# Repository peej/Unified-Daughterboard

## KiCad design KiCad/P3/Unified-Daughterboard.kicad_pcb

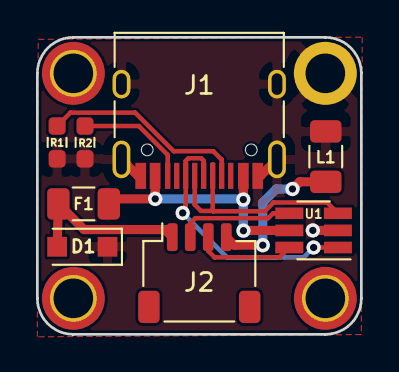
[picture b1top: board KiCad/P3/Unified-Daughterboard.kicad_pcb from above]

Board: 2 copper layers, 18.0 x 16.5 mm, 13 parts (1 on the bottom side), 10 nets.

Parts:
D1: SMF9.0CA; D_SOD-123F
F1: ASMD1206-150; Fuse_1206_3216Metric
G1: Unified-Daughterboard-Logo; Unified-Daughterboard-Logo.pretty
J1: USB_C_Receptacle_USB2.0; USB_C_Receptacle_HRO_TYPE-C-31-M-12
J2: SM04B-SRSS-TB(LF)(SN); JST_SH_SM04B-SRSS-TB_1x04-1MP_P1.00mm_Horizontal
L1: 60R@100MHz; L_1206_3216Metric
MH1, MH3, MH4: Mount-M2; MountingHole_2.2mm_M2_Pad_TopOnly
MH2: Mount-M2; MountingHole_2.2mm_M2_Pad
R1, R2: 5.1k; R_0603_1608Metric_Pad0.98x0.95mm_HandSolder
U1: USBLC6-2SC6; SOT-23-6_Handsoldering

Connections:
D+: J1.A6, J1.B6, U1.1
D-: J1.A7, J1.B7, U1.3
DN: J2.2, U1.4
DP: J2.3, U1.6
GND: J2.4, L1.1
GNDPWR: D1.1, J1.A1, J1.A12, J1.B1, J1.B12, J1.S1, L1.2, MH2.1, R1.2, R2.2, U1.2
unnamed: J1.A5, R1.1
unnamed: J1.B5, R2.1
VBUS: F1.1, J1.A4, J1.A9, J1.B4, J1.B9, U1.5
VCC: D1.2, F1.2, J2.1

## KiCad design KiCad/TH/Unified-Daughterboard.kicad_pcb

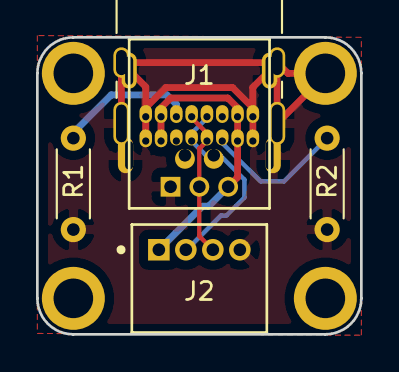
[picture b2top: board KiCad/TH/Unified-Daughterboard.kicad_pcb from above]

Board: 2 copper layers, 18.0 x 16.5 mm, 8 parts (0 on the bottom side), 6 nets.

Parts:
J1: HRO-TYPE-C-31-M-12; USB_Hybrid
J2: Conn_01x04; JST-S4B-ZRLFSN-0-0-MFG
MH1, MH2, MH3, MH4: Mount-M2; Generic-Mounthole
R1, R2: 5.1k; R_Axial_DIN0204_L3.6mm_D1.6mm_P5.08mm_Horizontal

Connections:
D+: J1.A6, J1.B6, J2.3
D-: J1.A7, J1.B7, J2.2
GND: J1.A1, J1.A12, J1.B1, J1.B12, J1.S1, J2.4, MH2.1, R1.2, R2.2
unnamed: J1.A5, R2.1
unnamed: J1.B5, R1.1
VCC: J1.A4, J1.A9, J1.B4, J1.B9, J2.1

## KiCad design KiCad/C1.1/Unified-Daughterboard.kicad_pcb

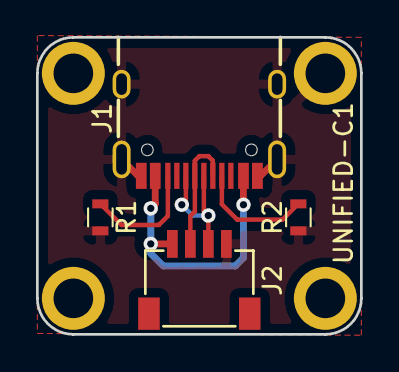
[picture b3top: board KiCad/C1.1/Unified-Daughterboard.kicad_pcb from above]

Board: 2 copper layers, 18.0 x 16.5 mm, 8 parts (0 on the bottom side), 6 nets.

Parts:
J1: HRO-TYPE-C-31-M-12; HRO-TYPE-C-31-M-12-Assembly
J2: Conn_01x04; JST-SR-4
MH1, MH2, MH3, MH4: Mount-M2; Generic-Mounthole
R1, R2: 5.1k; R_0603

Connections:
D+: J1.6, J1.8, J2.3
D-: J1.5, J1.7, J2.2
GND: J1.1, J1.12, J1.13, J2.4, MH2.1, R1.2, R2.2
unnamed: J1.4, R2.1
unnamed: J1.10, R1.1
VCC: J1.2, J1.11, J2.1

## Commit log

2021-09-17 Add C1 variant with ground plane
2021-12-02 Add P3 variant using USBLC6-2SC6 for ESD protection
2021-12-02 Add simple through hole variant
2021-12-02 Move vias off of pads
2021-12-04 Update P3 panel to improve mousebites and allow soldering before splitting
